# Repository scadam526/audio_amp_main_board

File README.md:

# audio_amp_main_board
Main board for a stereo 60W-per-channel amp. Includes four RCA analog L/R inputs, pre-amp input switching and volume control, main gain stage and output protection and muting.

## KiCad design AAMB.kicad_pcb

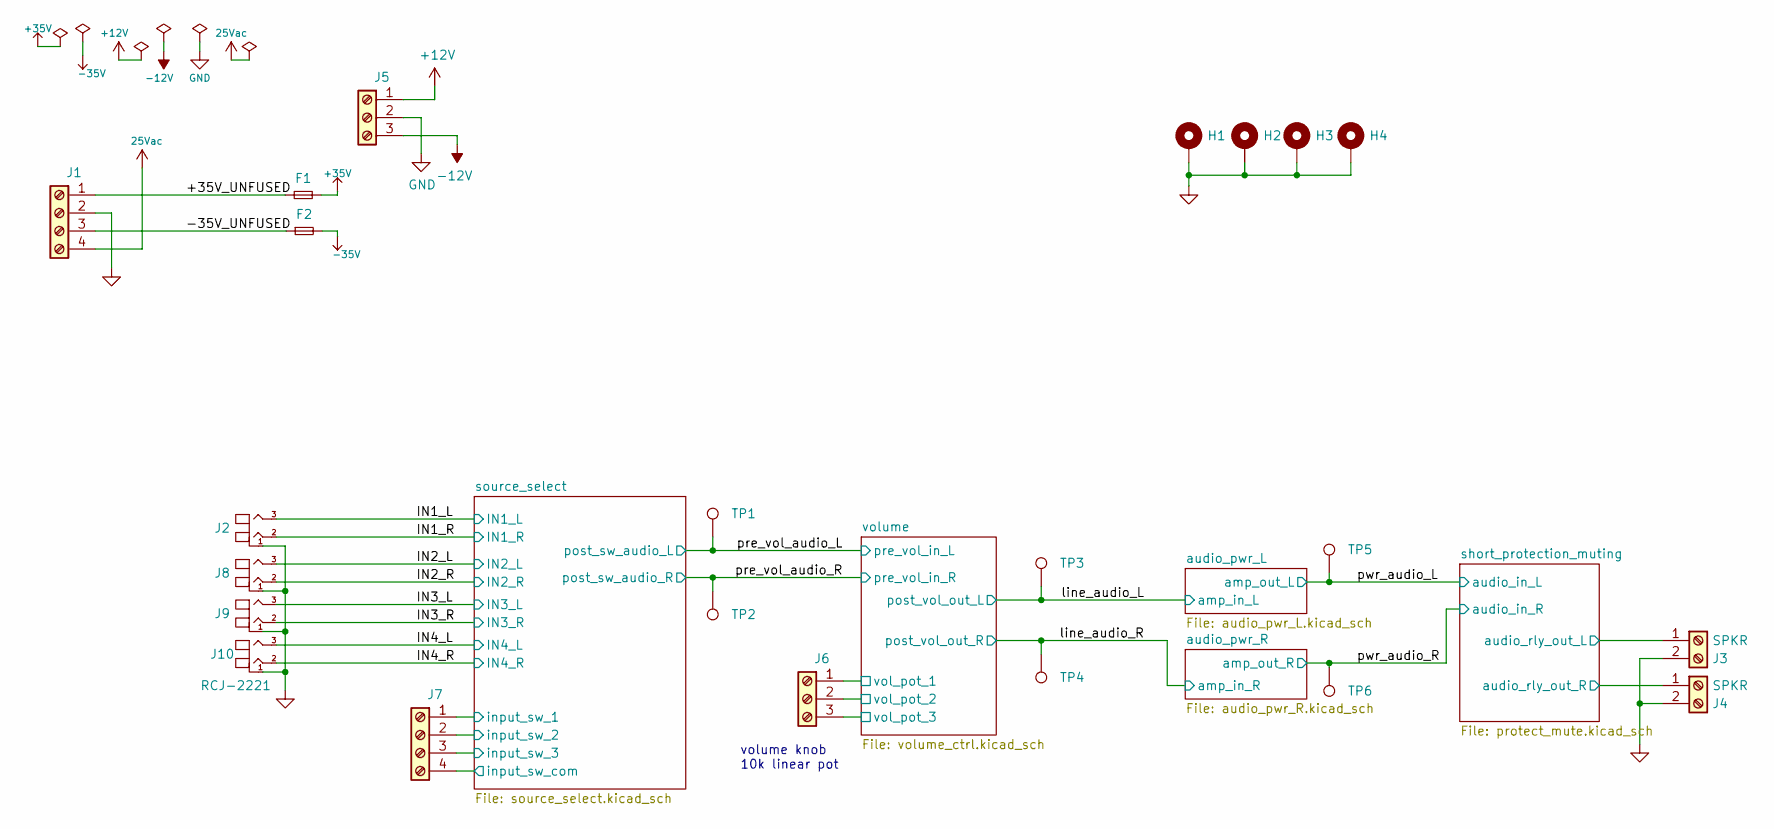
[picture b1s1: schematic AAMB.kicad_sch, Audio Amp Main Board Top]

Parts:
F1, F2: Fuse_Small; R_1206_3216Metric_Pad1.30x1.75mm_HandSolder; MPN C1F 3
H1, H2, H3, H4: MountingHole_Pad; MountingHole_3.2mm_M3_Pad
J1, J7: Screw_Terminal_01x04; TerminalBlock_Phoenix_MKDS-1,5-4_1x04_P5.00mm_Horizontal; MPN TB001-500-04BE
J2, J8, J9, J10: RCJ-2221
J3, J4: SPKR; TerminalBlock_Phoenix_MKDS-1,5-2_1x02_P5.00mm_Horizontal; MPN 1935161
J5, J6: Screw_Terminal_01x03; TerminalBlock_Phoenix_MKDS-1,5-3_1x03_P5.00mm_Horizontal; MPN 1935174
TP1, TP2, TP3, TP4, TP5, TP6: TestPoint; TestPoint_Keystone_5000-5004_Miniature

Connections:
25Vac: J1.4; also elsewhere on the board
+12V: J5.1; also elsewhere on the board
+35V: F1.2; also elsewhere on the board
-12V: J5.3; also elsewhere on the board
-35V: F2.2; also elsewhere on the board
/+35V_UNFUSED: F1.1, J1.1
/-35V_UNFUSED: F2.1, J1.3
/IN1_L: J2.3; also elsewhere on the board
/IN1_R: J2.2; also elsewhere on the board
/IN2_L: J8.3; also elsewhere on the board
/IN2_R: J8.2; also elsewhere on the board
/IN3_L: J9.3; also elsewhere on the board
/IN3_R: J9.2; also elsewhere on the board
/IN4_L: J10.3; also elsewhere on the board
/IN4_R: J10.2; also elsewhere on the board
/line_audio_L: TP3.1; also elsewhere on the board
/line_audio_R: TP4.1; also elsewhere on the board
/pre_vol_audio_L: TP1.1; also elsewhere on the board
/pre_vol_audio_R: TP2.1; also elsewhere on the board
/pwr_audio_L: TP5.1; also elsewhere on the board
/pwr_audio_R: TP6.1; also elsewhere on the board
/short_protection_muting/audio_rly_out_L: J3.1; also elsewhere on the board
/short_protection_muting/audio_rly_out_R: J4.1; also elsewhere on the board
/source_select/input_sw_1: J7.1; also elsewhere on the board
/source_select/input_sw_2: J7.2; also elsewhere on the board
/source_select/input_sw_3: J7.3; also elsewhere on the board
/source_select/input_sw_com: J7.4; also elsewhere on the board
/volume/vol_pot_1: J6.1; also elsewhere on the board
/volume/vol_pot_2: J6.2; also elsewhere on the board
/volume/vol_pot_3: J6.3; also elsewhere on the board
GND: H1.1, H2.1, H3.1, H4.1, J1.2, J2.1, J3.2, J4.2, J5.2, J8.1, J9.1, J10.1; also elsewhere on the board

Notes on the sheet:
volume knob 10k linear pot

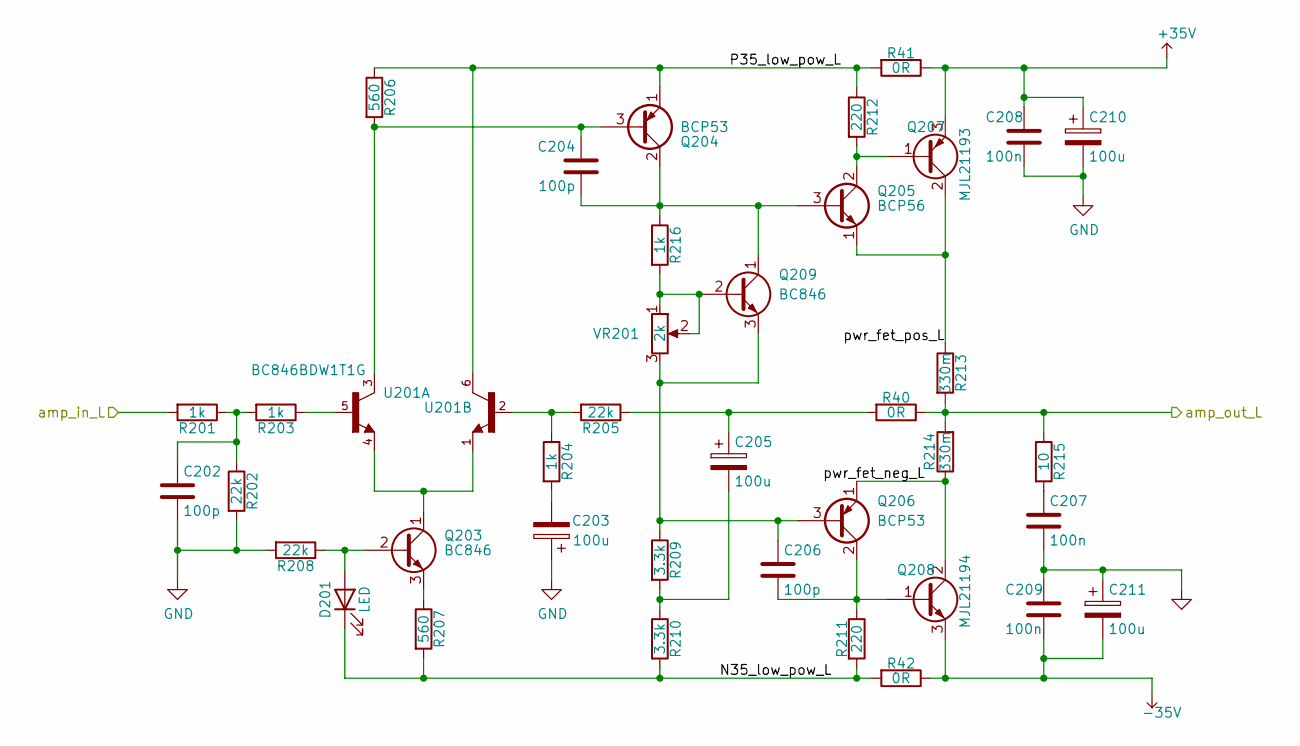
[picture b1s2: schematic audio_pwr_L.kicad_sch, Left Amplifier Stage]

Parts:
C202, C204, C206: 100p; C_0603_1608Metric_Pad1.08x0.95mm_HandSolder; MPN 885012006057
C203: 100u; C_Elec_5x5.4; MPN 865080142007
C205: 100u; C_Elec_6.3x7.7; MPN 865080545012
C207, C208, C209: 100n; C_Rect_L7.2mm_W4.5mm_P5.00mm_FKS2_FKP2_MKS2_MKP2; MPN R82EC3100AA70K
C210, C211: 100u; CP_Elec_10x10.5; MPN UUX1J101MNL1GS
D201: LED; LED_0603_1608Metric_Pad1.05x0.95mm_HandSolder; MPN SML-D12U1WT86
Q203, Q209: BC846; TO-92_Molded_Narrow; MPN BC846BLT1G
Q204, Q206: BCP53; TO-126_Vertical; MPN SBCP53-10T1G
Q205: BCP56; TO-126_Vertical; MPN SBCP56-16T3G
Q207: MJL21193; TO-264-3_Vertical; MPN MJL21193G
Q208: MJL21194; TO-264-3_Vertical; MPN MJL21194G
R40, R41, R42: 0R; R_2010_5025Metric; MPN RMCF1210ZT0R00
R201, R203, R204, R216: 1k; R_0201_0603Metric_Pad0.64x0.40mm_HandSolder; MPN RCS06031K00FKEA
R202, R205, R208: 22k; R_0201_0603Metric_Pad0.64x0.40mm_HandSolder; MPN CRGCQ0603F22K
R206, R207: 560; R_0201_0603Metric_Pad0.64x0.40mm_HandSolder; MPN CRGCQ0603F560R
R209, R210: 3.3k; R_0201_0603Metric_Pad0.64x0.40mm_HandSolder; MPN CRCW06033K30FKEA
R211, R212: 220; R_0201_0603Metric_Pad0.64x0.40mm_HandSolder; MPN ERJ-PA3F2200V
R213, R214: 330m; R_Radial_Power_L13.0mm_W9.0mm_P5.00mm; MPN SQMW5R33J
R215: 10; R_0201_0603Metric_Pad0.64x0.40mm_HandSolder; MPN ERJ-PA3F10R0V
U201: BC846BDW1T1G; SOT65P210X110-6N; MPN BC846BDW1T1G
VR201: 2k; Potentiometer_Bourns_3296W_Vertical; MPN 3296W-1-202LF

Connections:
+35V: C208.1, C210.1, Q207.3 (E), R41.1; also elsewhere on the board
-35V: C209.2, C211.2, Q208.3 (E), R42.1; also elsewhere on the board
/audio_pwr_L/N35_low_pow_L: D201.1 (K), R42.2, R207.2, R210.2, R211.2
/audio_pwr_L/P35_low_pow_L: Q204.1 (E), R41.2, R206.1, R212.1, U201.6 (COLLECTOR_2)
/audio_pwr_L/pwr_fet_neg_L: Q206.1 (E), Q208.2 (C), R214.1
/audio_pwr_L/pwr_fet_pos_L: Q205.1 (E), Q207.2 (C), R213.1
/line_audio_L: R201.2; also elsewhere on the board
/pwr_audio_L: R40.1, R213.2, R214.2, R215.1; also elsewhere on the board
GND: C202.2, C203.1, C207.2, C208.2, C209.1, C210.2, C211.1, R202.2, R208.2; also elsewhere on the board
unnamed: C202.1, R201.1, R202.1, R203.2
unnamed: C203.2, R204.2
unnamed: C204.1, Q204.3 (B), R206.2, U201.3 (COLLECTOR_1)
unnamed: C204.2, Q204.2 (C), Q205.3 (B), Q209.1 (C), R216.1
unnamed: C205.1, R40.2, R205.1
unnamed: C205.2, R209.2, R210.1
unnamed: C206.1, Q206.3 (B), Q209.3 (E), R209.1, VR201.3
unnamed: C206.2, Q206.2 (C), Q208.1 (B), R211.1
unnamed: C207.1, R215.2
unnamed: D201.2 (A), Q203.2 (B), R208.1
unnamed: Q203.1 (C), U201.1 (EMITTER_2), U201.4 (EMITTER_1)
unnamed: Q203.3 (E), R207.1
unnamed: Q205.2 (C), Q207.1 (B), R212.2
unnamed: Q209.2 (B), R216.2, VR201.1, VR201.2
unnamed: R203.1, U201.5 (BASE_1)
unnamed: R204.1, R205.2, U201.2 (BASE_2)

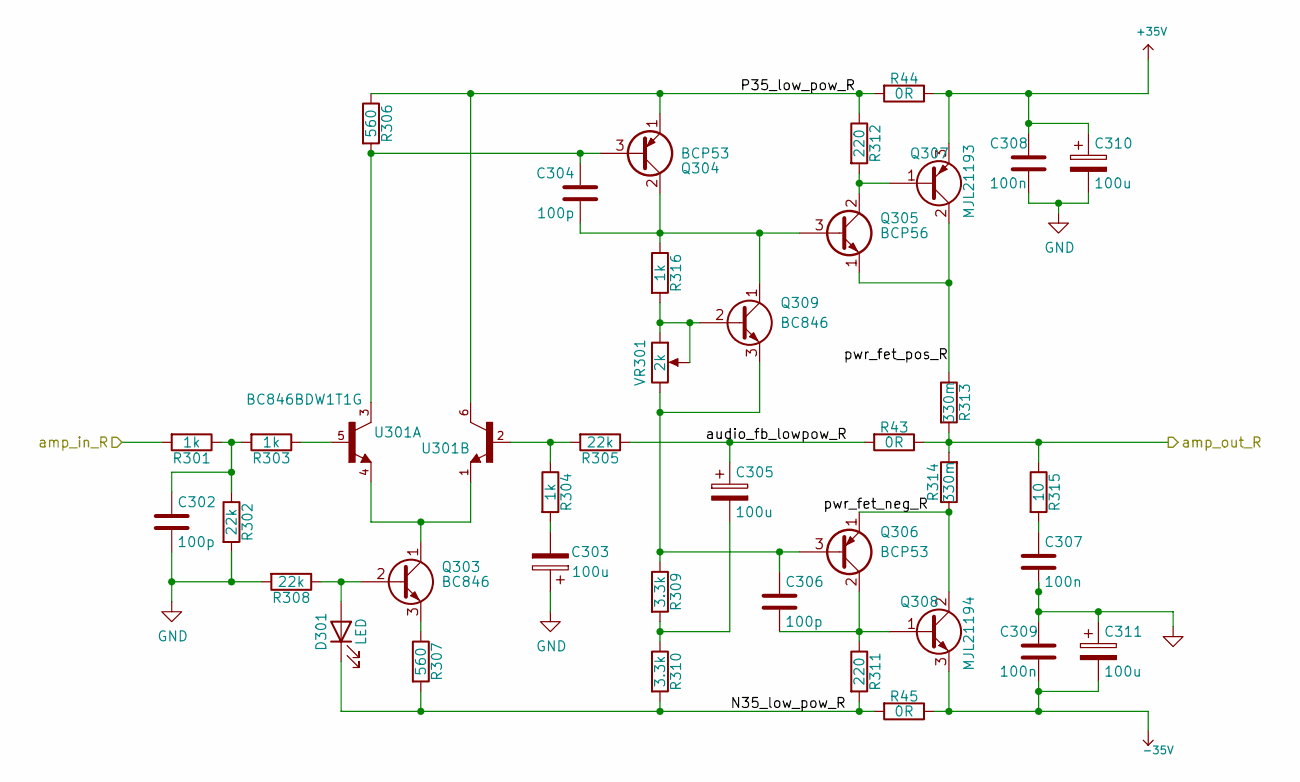
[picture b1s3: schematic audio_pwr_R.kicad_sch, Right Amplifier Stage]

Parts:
C302, C304, C306: 100p; C_0603_1608Metric_Pad1.08x0.95mm_HandSolder; MPN 885012006057
C303: 100u; C_Elec_5x5.4; MPN 865080142007
C305: 100u; C_Elec_6.3x7.7; MPN 865080545012
C307, C308, C309: 100n; C_Rect_L7.2mm_W4.5mm_P5.00mm_FKS2_FKP2_MKS2_MKP2; MPN R82EC3100AA70K
C310, C311: 100u; CP_Elec_10x10.5; MPN UUX1J101MNL1GS
D301: LED; LED_0603_1608Metric_Pad1.05x0.95mm_HandSolder; MPN SML-D12U1WT86
Q303, Q309: BC846; TO-92_Molded_Narrow; MPN BC846BLT1G
Q304, Q306: BCP53; TO-126_Vertical; MPN SBCP53-10T1G
Q305: BCP56; TO-126_Vertical; MPN SBCP56-16T3G
Q307: MJL21193; TO-264-3_Vertical; MPN MJL21193G
Q308: MJL21194; TO-264-3_Vertical; MPN MJL21194G
R43, R44, R45: 0R; R_2010_5025Metric; MPN RMCF1210ZT0R00
R301, R303, R304, R316: 1k; R_0201_0603Metric_Pad0.64x0.40mm_HandSolder; MPN RCS06031K00FKEA
R302, R305, R308: 22k; R_0201_0603Metric_Pad0.64x0.40mm_HandSolder; MPN CRGCQ0603F22K
R306, R307: 560; R_0201_0603Metric_Pad0.64x0.40mm_HandSolder; MPN CRGCQ0603F560R
R309, R310: 3.3k; R_0201_0603Metric_Pad0.64x0.40mm_HandSolder; MPN CRCW06033K30FKEA
R311, R312: 220; R_0201_0603Metric_Pad0.64x0.40mm_HandSolder; MPN ERJ-PA3F2200V
R313, R314: 330m; R_Radial_Power_L13.0mm_W9.0mm_P5.00mm; MPN SQMW5R33J
R315: 10; R_0201_0603Metric_Pad0.64x0.40mm_HandSolder; MPN ERJ-PA3F10R0V
U301: BC846BDW1T1G; SOT65P210X110-6N; MPN BC846BDW1T1G
VR301: 2k; Potentiometer_Bourns_3296W_Vertical; MPN 3296W-1-202LF

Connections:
+35V: C308.1, C310.1, Q307.3 (E), R44.1; also elsewhere on the board
-35V: C309.2, C311.2, Q308.3 (E), R45.1; also elsewhere on the board
/audio_pwr_R/N35_low_pow_R: D301.1 (K), R45.2, R307.2, R310.2, R311.2
/audio_pwr_R/P35_low_pow_R: Q304.1 (E), R44.2, R306.1, R312.1, U301.6 (COLLECTOR_2)
/audio_pwr_R/pwr_fet_neg_R: Q306.1 (E), Q308.2 (C), R314.1
/audio_pwr_R/pwr_fet_pos_R: Q305.1 (E), Q307.2 (C), R313.1
/line_audio_R: R301.2; also elsewhere on the board
/pwr_audio_R: R43.1, R313.2, R314.2, R315.1; also elsewhere on the board
GND: C302.2, C303.1, C307.2, C308.2, C309.1, C310.2, C311.1, R302.2, R308.2; also elsewhere on the board
unnamed: C302.1, R301.1, R302.1, R303.2
unnamed: C303.2, R304.2
unnamed: C304.1, Q304.3 (B), R306.2, U301.3 (COLLECTOR_1)
unnamed: C304.2, Q304.2 (C), Q305.3 (B), Q309.1 (C), R316.1
unnamed: C305.1, R43.2, R305.1
unnamed: C305.2, R309.2, R310.1
unnamed: C306.1, Q306.3 (B), Q309.3 (E), R309.1, VR301.3
unnamed: C306.2, Q306.2 (C), Q308.1 (B), R311.1
unnamed: C307.1, R315.2
unnamed: D301.2 (A), Q303.2 (B), R308.1
unnamed: Q303.1 (C), U301.1 (EMITTER_2), U301.4 (EMITTER_1)
unnamed: Q303.3 (E), R307.1
unnamed: Q305.2 (C), Q307.1 (B), R312.2
unnamed: Q309.2 (B), R316.2, VR301.1, VR301.2
unnamed: R303.1, U301.5 (BASE_1)
unnamed: R304.1, R305.2, U301.2 (BASE_2)

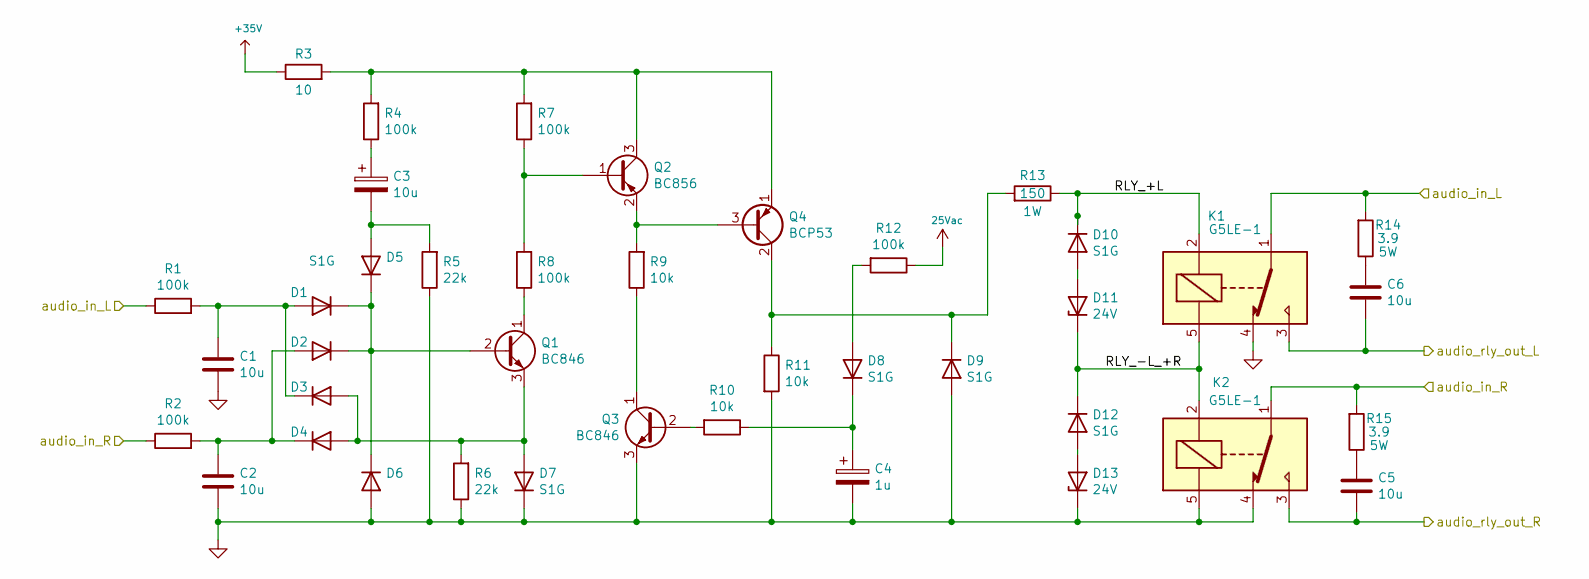
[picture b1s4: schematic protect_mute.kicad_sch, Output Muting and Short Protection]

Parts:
C1, C2, C5, C6: 10u; C_1206_3216Metric; MPN GRT31CR61H106KE01L
C3: 10u; CP_Elec_5x3; MPN 865080642006
C4: 1u; CP_Elec_4x5.4; MPN 865060640001
D1, D2, D3, D4, D5, D6, D7, D8, D9, D10, D12: S1G; D_DO-41_SOD81_P10.16mm_Horizontal; MPN S1G
D11, D13: 24V; D_SMA; MPN 1SMA5934BT3G
K1, K2: G5LE-1; Relay_SPDT_Omron-G5LE-1; MPN G5LE-1-VDDC12
Q1, Q3: BC846; TO-92_Inline; MPN BC846BLT1G
Q2: BC856; SOT-23; MPN BC856BLT3G
Q4: BCP53; TO-126-3_Vertical; MPN SBCP53-10T1G
R1, R2, R4, R7, R8, R12: 100k; R_0201_0603Metric_Pad0.64x0.40mm_HandSolder; MPN MCT06030C1003FP500
R3: 10; R_0201_0603Metric_Pad0.64x0.40mm_HandSolder; MPN ERJ-PA3F10R0V
R5, R6: 22k; R_0201_0603Metric_Pad0.64x0.40mm_HandSolder; MPN CRGCQ0603F22K
R9, R10, R11: 10k; R_0201_0603Metric_Pad0.64x0.40mm_HandSolder; MPN CRGCQ0603F10K
R13: 150; R_2512_6332Metric; MPN CRCW2512150RFKEG
R14, R15: 3.9; R_Axial_DIN0918_L18.0mm_D9.0mm_P7.62mm_Vertical; MPN SQPW53R9J

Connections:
25Vac: R12.1; also elsewhere on the board
+35V: R3.1; also elsewhere on the board
/pwr_audio_L: K1.1, R1.1, R14.2; also elsewhere on the board
/pwr_audio_R: K2.1, R2.1, R15.2; also elsewhere on the board
/short_protection_muting/RLY_+L: D10.1 (K), K1.2, R13.1
/short_protection_muting/RLY_-L_+R: D11.1 (K), D12.1 (K), K1.5, K2.2
/short_protection_muting/audio_rly_out_L: C6.2, K1.3; also elsewhere on the board
/short_protection_muting/audio_rly_out_R: C5.2, K2.3; also elsewhere on the board
GND: C1.2, C2.2, C4.2, D6.2 (A), D7.1 (K), D9.2 (A), D13.1 (K), K1.4, K2.4, K2.5, Q3.3 (E), R5.1, R6.1, R11.2; also elsewhere on the board
unnamed: C1.1, D1.2 (A), D3.1 (K), R1.2
unnamed: C2.1, D2.2 (A), D4.1 (K), R2.2
unnamed: C3.1, R4.1
unnamed: C3.2, D5.2 (A), R5.2
unnamed: C4.1, D8.1 (K), R10.1
unnamed: C5.1, R15.1
unnamed: C6.1, R14.1
unnamed: D1.1 (K), D2.1 (K), D5.1 (K), D6.1 (K), Q1.2 (B)
unnamed: D3.2 (A), D4.2 (A), D7.2 (A), Q1.3 (E), R6.2
unnamed: D8.2 (A), R12.2
unnamed: D9.1 (K), Q4.2 (C), R11.1, R13.2
unnamed: D10.2 (A), D11.2 (A)
unnamed: D12.2 (A), D13.2 (A)
unnamed: Q1.1 (C), R8.1
unnamed: Q2.1 (B), R7.1, R8.2
unnamed: Q2.2 (E), Q4.3 (B), R9.2
unnamed: Q2.3 (C), Q4.1 (E), R3.2, R4.2, R7.2
unnamed: Q3.1 (C), R9.1
unnamed: Q3.2 (B), R10.2

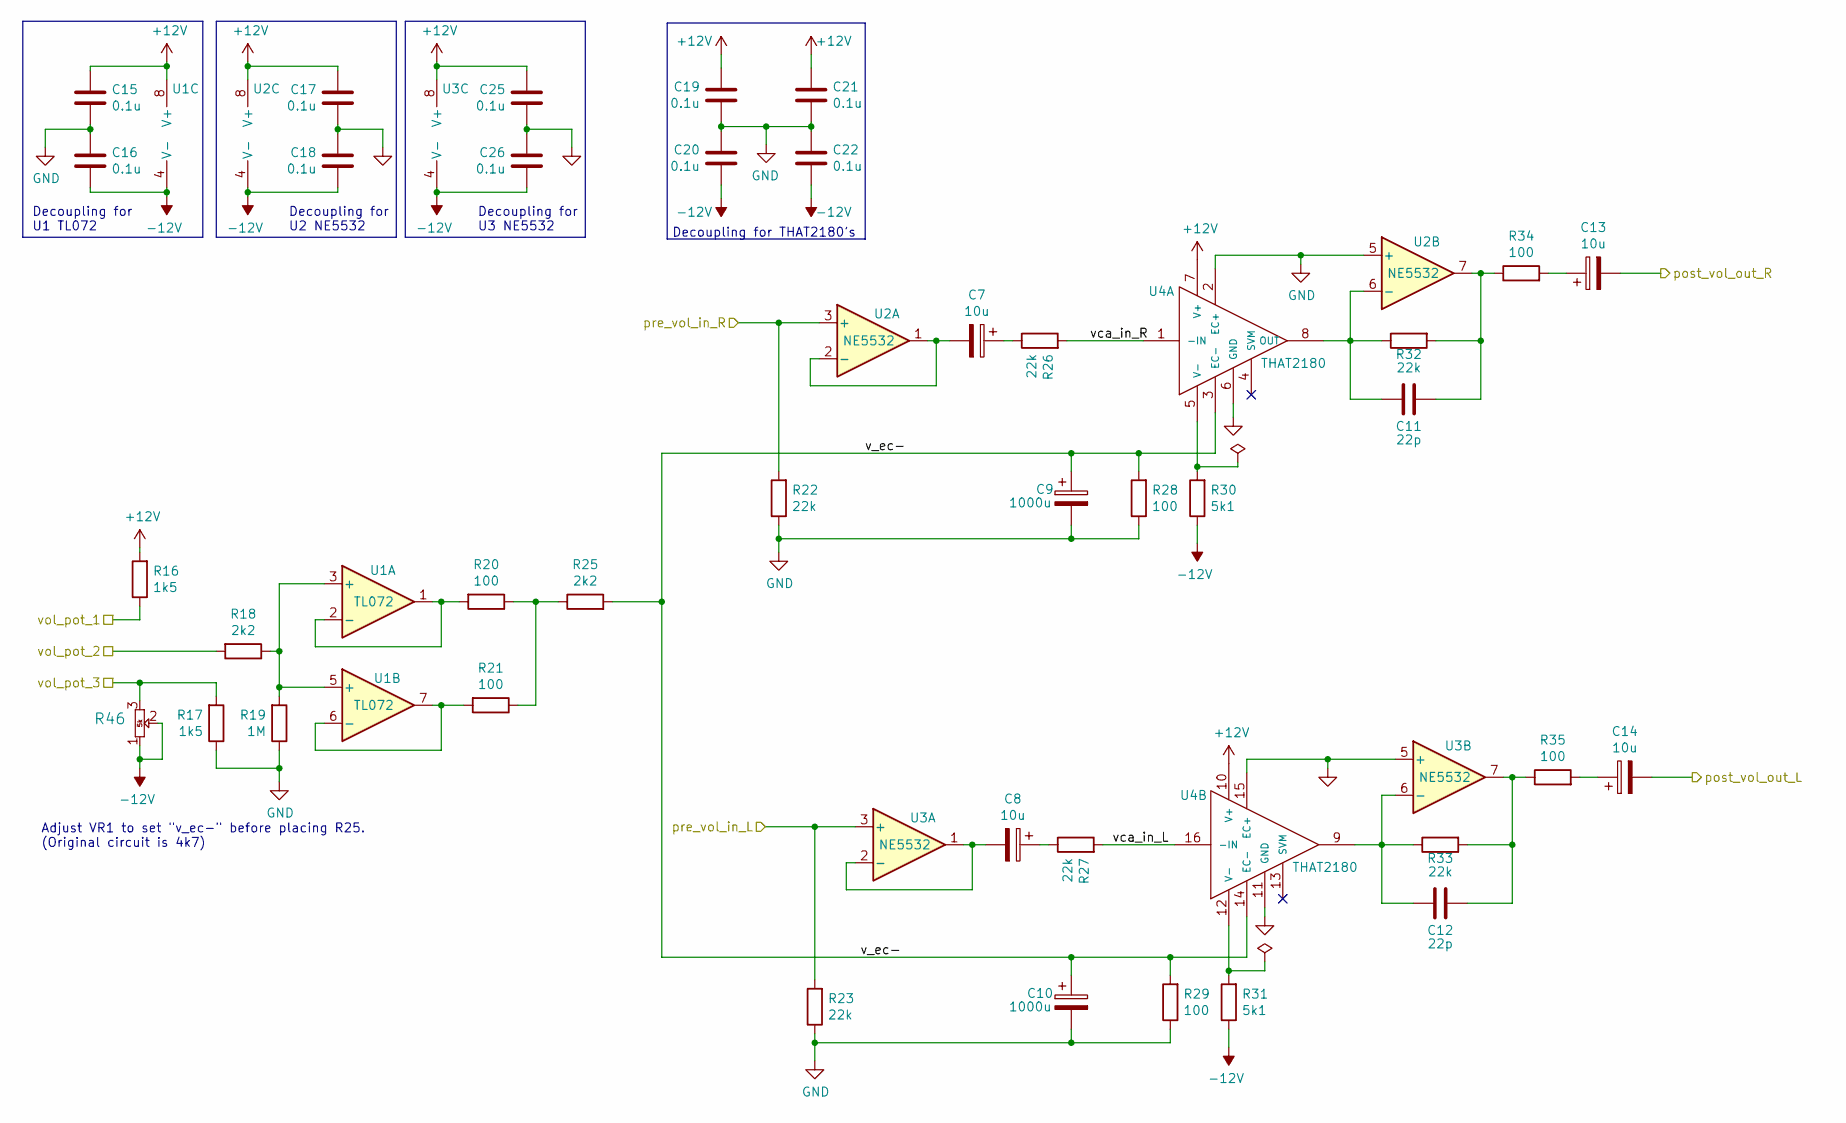
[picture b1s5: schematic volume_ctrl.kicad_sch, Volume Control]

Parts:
C7, C8, C13, C14: 10u; CP_Elec_5x3; MPN 865080642006
C9, C10: 1000u; C_Elec_10x10.2; MPN EEV-FK1E102Q
C11, C12: 22p; C_0603_1608Metric_Pad1.08x0.95mm_HandSolder; MPN 885012006053
C15, C16, C17, C18, C19, C20, C21, C22, C25, C26: 0.1u; C_0603_1608Metric_Pad1.08x0.95mm_HandSolder; MPN C0603C104Z3VACTU
R16, R17: 1k5; R_0201_0603Metric_Pad0.64x0.40mm_HandSolder; MPN ERJ-3EKF1501V
R18, R25: 2k2; R_0201_0603Metric_Pad0.64x0.40mm_HandSolder; MPN CRGCQ0603F2K2
R19: 1M; R_0201_0603Metric_Pad0.64x0.40mm_HandSolder; MPN ERJ-3EKF1004V
R20, R21, R28, R29, R34, R35: 100; R_0201_0603Metric_Pad0.64x0.40mm_HandSolder; MPN RCS0603100RFKEA
R22, R23, R26, R27, R32, R33: 22k; R_0201_0603Metric_Pad0.64x0.40mm_HandSolder; MPN CRGCQ0603F22K
R30, R31: 5k1; R_0201_0603Metric_Pad0.64x0.40mm_HandSolder; MPN ERJ-PA3F5101V
R46: 3203X502P; 3203X502P_TEC
U1: TL072; SOIC-8_3.9x4.9mm_P1.27mm; MPN TL072CDT
U2, U3: NE5532; SOIC-8_3.9x4.9mm_P1.27mm; MPN NE5532DR
U4: THAT2180; DIP-16_W7.62mm_SMDSocket_SmallPads; MPN 214-99-316-01-670800

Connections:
+12V: C15.1, C17.1, C19.1, C21.1, C25.1, R16.2, U1.8 (V+), U2.8 (V+), U3.8 (V+), U4.7 (V+), U4.10 (V+); also elsewhere on the board
-12V: C16.2, C18.2, C20.2, C22.2, C26.2, R30.1, R31.1, R46.1, R46.2, U1.4 (V-), U2.4 (V-), U3.4 (V-); also elsewhere on the board
/line_audio_L: C14.2; also elsewhere on the board
/line_audio_R: C13.2; also elsewhere on the board
/pre_vol_audio_L: R23.2, U3.3 (+); also elsewhere on the board
/pre_vol_audio_R: R22.2, U2.3 (+); also elsewhere on the board
/volume/v_ec-: C9.1, C10.1, R25.2, R28.2, R29.2, U4.3 (EC-), U4.14 (EC-)
/volume/vca_in_L: R27.2, U4.16 (-IN)
/volume/vca_in_R: R26.2, U4.1 (-IN)
/volume/vol_pot_1: R16.1; also elsewhere on the board
/volume/vol_pot_2: R18.2; also elsewhere on the board
/volume/vol_pot_3: R17.2, R46.3; also elsewhere on the board
GND: C9.2, C10.2, C15.2, C16.1, C17.2, C18.1, C19.2, C20.1, C21.2, C22.1, C25.2, C26.1, R17.1, R19.1, R22.1, R23.1, R28.1, R29.1, U2.5 (+), U3.5 (+), U4.2 (EC+), U4.6 (GND), U4.11 (GND), U4.15 (EC+); also elsewhere on the board
unnamed: C7.1, R26.1
unnamed: C7.2, U2.1, U2.2 (-)
unnamed: C8.1, R27.1
unnamed: C8.2, U3.1, U3.2 (-)
unnamed: C11.1, R32.2, R34.1, U2.7
unnamed: C11.2, R32.1, U2.6 (-), U4.8 (OUT)
unnamed: C12.1, R33.2, R35.1, U3.7
unnamed: C12.2, R33.1, U3.6 (-), U4.9
unnamed: C13.1, R34.2
unnamed: C14.1, R35.2
unnamed: R18.1, R19.2, U1.3 (+), U1.5 (+)
unnamed: R20.1, R21.1, R25.1
unnamed: R20.2, U1.1, U1.2 (-)
unnamed: R21.2, U1.6 (-), U1.7
unnamed: R30.2, U4.5 (V-)
unnamed: R31.2, U4.12 (V-)

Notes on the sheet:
Adjust VR1 to set "v_ec-" before placing R25. (Original circuit is 4k7)
Decoupling for U1 TL072
Decoupling for U2 NE5532
Decoupling for U3 NE5532
Decoupling for THAT2180's

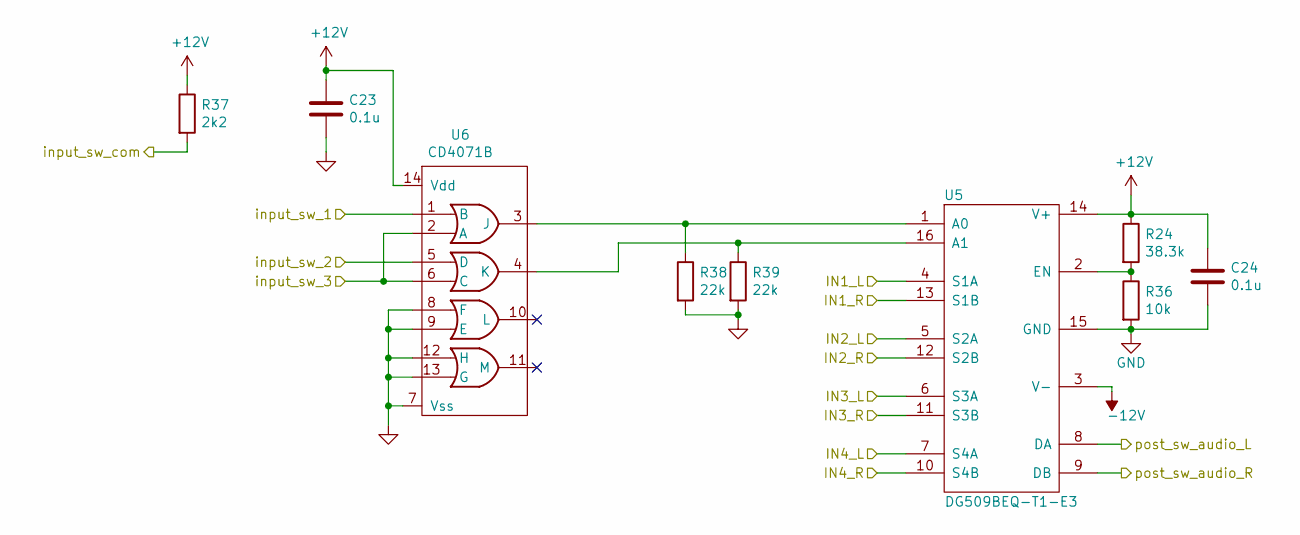
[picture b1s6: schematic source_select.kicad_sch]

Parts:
C23, C24: 0.1u; C_0603_1608Metric_Pad1.08x0.95mm_HandSolder; MPN C0603C104Z3VACTU
R24: 38.3k; R_0201_0603Metric_Pad0.64x0.40mm_HandSolder; MPN ERJ-3EKF3832V
R36: 10k; R_0201_0603Metric_Pad0.64x0.40mm_HandSolder; MPN CRGCQ0603F10K
R37: 2k2; R_0201_0603Metric_Pad0.64x0.40mm_HandSolder; MPN CRGCQ0603F2K2
R38, R39: 22k; R_0201_0603Metric_Pad0.64x0.40mm_HandSolder; MPN CRGCQ0603F22K
U5: DG509BEQ-T1-E3; TSSOP-16_4.4x5mm_P0.65mm; MPN DG509BEQ-T1-E3
U6: CD4071B; SOIC-14_3.9x8.7mm_P1.27mm; MPN CD4071BM96

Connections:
+12V: C23.1, C24.1, R24.1, R37.1, U5.14 (V+), U6.14 (Vdd); also elsewhere on the board
-12V: U5.3 (V-); also elsewhere on the board
/IN1_L: U5.4 (S1A); also elsewhere on the board
/IN1_R: U5.13 (S1B); also elsewhere on the board
/IN2_L: U5.5 (S2A); also elsewhere on the board
/IN2_R: U5.12 (S2B); also elsewhere on the board
/IN3_L: U5.6 (S3A); also elsewhere on the board
/IN3_R: U5.11 (S3B); also elsewhere on the board
/IN4_L: U5.7 (S4A); also elsewhere on the board
/IN4_R: U5.10 (S4B); also elsewhere on the board
/pre_vol_audio_L: U5.8 (DA); also elsewhere on the board
/pre_vol_audio_R: U5.9 (DB); also elsewhere on the board
/source_select/input_sw_1: U6.1 (B); also elsewhere on the board
/source_select/input_sw_2: U6.5 (D); also elsewhere on the board
/source_select/input_sw_3: U6.2 (A), U6.6 (C); also elsewhere on the board
/source_select/input_sw_com: R37.2; also elsewhere on the board
GND: C23.2, C24.2, R36.2, R38.2, R39.2, U5.15 (GND), U6.7 (Vss), U6.8 (F), U6.9 (E), U6.12 (H), U6.13 (G); also elsewhere on the board
unnamed: R24.2, R36.1, U5.2 (EN)
unnamed: R38.1, U5.1 (A0), U6.3 (J)
unnamed: R39.1, U5.16 (A1), U6.4 (K)

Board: 6 copper layers, 191 parts (26 on the bottom side), 114 nets, no tracks yet.

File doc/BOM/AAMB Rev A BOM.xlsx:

Ref | Qnty | MFG | MPN | Value | Footprint
C1, C5, C6, C2, | 4 | Murata Electronics | GRT31CR61H106KE01L | 10u | Capacitor_SMD:C_1206_3216Metric
C4, | 1 | Wurth Elektronik | 865060640001 | 1u | Capacitor_SMD:CP_Elec_4x5.4
C8, C14, C7, C13, C3, | 5 | Wurth Elektronik | 865080642006 | 10u | Capacitor_SMD:CP_Elec_5x3
C9, C10, | 2 | Panasonic Electronic Components | EEV-FK1E102Q | 1000u | Capacitor_SMD:C_Elec_10x10.2
C12, C11, | 2 | Wurth Elektronik | 885012006053 | 22p | Capacitor_SMD:C_0603_1608Metric_Pad1.05x0.95mm_HandSolder
C15, C16, C17, C18, C19, C20, C21, C22, C25, C26, C23, C24, | 12 | KEMET | C0603C104Z3VACTU | 0.1u | Capacitor_SMD:C_0603_1608Metric_Pad1.05x0.95mm_HandSolder
C202, C206, C204, C302, C306, C304, | 6 | Wurth Elektronik | 885012006057 | 100p | Capacitor_SMD:C_0603_1608Metric_Pad1.05x0.95mm_HandSolder
C203, C303, | 2 | Wurth Elektronik | 865080142007 | 100u | Capacitor_SMD:C_Elec_5x5.4
C205, C305, | 2 | Wurth Elektronik | 865080545012 | 100u | Capacitor_SMD:C_Elec_6.3x7.7
C207, C209, C208, C307, C309, C308, | 6 | KEMET | R82EC3100AA70K | 100n | Capacitor_THT:C_Rect_L7.2mm_W4.5mm_P5.00mm_FKS2_FKP2_MKS2_MKP2
C211, C210, C311, C310, | 4 | Nichicon | UUX1J101MNL1GS | 100u | Capacitor_SMD:CP_Elec_10x10.5
D12, D10, D5, D9, D8, D7, D6, D4, D3, D2, D1, | 11 | ON Semiconductor | S1G | S1G | Diode_SMD:D_SMA
D13, D11, | 2 | ON Semiconductor | 1SMA5934BT3G | 24V | Diode_SMD:D_SMA
D201, D301, | 2 | Rohm Semiconductor | SML-D12U1WT86 | LED | LED_SMD:LED_0603_1608Metric_Pad1.05x0.95mm_HandSolder
F2, F1, | 2 | Bel Fuse Inc. | C1F 3 | Fuse_Small | Resistor_SMD:R_1206_3216Metric_Pad1.42x1.75mm_HandSolder
J1, J7, | 2 | CUI Devices | TB001-500-04BE | Screw_Terminal_01x04 | TerminalBlock_Phoenix:TerminalBlock_Phoenix_MKDS-1,5-4_1x04_P5.00mm_Horizontal
J2, | 1 | Switchcraft Inc. | PJRAS4X2U01X | PJRAS4X2U01X | Connectors-amp:PJRAS4X2U01X
J4, J3, | 2 | Phoenix Contact | 1935161 | SPKR | TerminalBlock_Phoenix:TerminalBlock_Phoenix_MKDS-1,5-2_1x02_P5.00mm_Horizontal
J5, J6, | 2 | Phoenix Contact | 1935174 | Screw_Terminal_01x03 | TerminalBlock_Phoenix:TerminalBlock_Phoenix_MKDS-1,5-3_1x03_P5.00mm_Horizontal
K2, K1, | 2 | Omron Electronics Inc-EMC Div | G5LE-1-VDDC12 | G5LE-1 | Relay_THT:Relay_SPDT_Omron-G5LE-1
Q2, | 1 | ON Semiconductor | BC856BLT3G | BC856 | Package_TO_SOT_SMD:SOT-23
Q203, Q209, Q303, Q309, Q3, Q1, | 6 | ON Semiconductor | BC846BLT1G | BC846 | Package_TO_SOT_SMD:SOT-23
Q205, Q305, | 2 | ON Semiconductor | SBCP56-16T3G | BCP56 | Package_TO_SOT_SMD:SOT-223
Q206, Q204, Q306, Q304, Q4, | 5 | ON Semiconductor | SBCP53-10T1G | BCP53 | Package_TO_SOT_SMD:SOT-223
Q207, Q307, | 2 | ON Semiconductor | MJL21193G | MJL21193 | Package_TO_SOT_THT:TO-264-3_Vertical
Q208, Q308, | 2 | ON Semiconductor | MJL21194G | MJL21194 | Package_TO_SOT_THT:TO-264-3_Vertical
R2, R1, R7, R4, R8, R12, | 6 | Vishay Beyschlag | MCT06030C1003FP500 | 100k | Resistor_SMD:R_0603_1608Metric_Pad1.05x0.95mm_HandSolder
R13, | 1 | Vishay Dale | CRCW2512150RFKEG | 150 | Resistor_SMD:R_2512_6332Metric
R14, R15, | 2 | TE Connectivity Passive Product | SQPW53R9J | 3.9 | Resistor_THT:R_Axial_DIN0918_L18.0mm_D9.0mm_P7.62mm_Vertical
R16, R17, | 2 | Panasonic Electronic Components | ERJ-3EKF1501V | 1k5 | Resistor_SMD:R_0603_1608Metric_Pad1.05x0.95mm_HandSolder
R19, | 1 | Panasonic Electronic Components | ERJ-3EKF1004V | 1M | Resistor_SMD:R_0603_1608Metric_Pad1.05x0.95mm_HandSolder
R24, | 1 | Panasonic Electronic Components | ERJ-3EKF3832V | 38.3k | Resistor_SMD:R_0603_1608Metric_Pad1.05x0.95mm_HandSolder
R25, R18, R37, | 3 | TE Connectivity Passive Product | CRGCQ0603F2K2 | 2k2 | Resistor_SMD:R_0603_1608Metric_Pad1.05x0.95mm_HandSolder
R31, R30, | 2 | Panasonic Electronic Components | ERJ-PA3F5101V | 5k1 | Resistor_SMD:R_0603_1608Metric_Pad1.05x0.95mm_HandSolder
R35, R20, R21, R29, R34, R28, | 6 | Vishay Dale | RCS0603100RFKEA | 100 | Resistor_SMD:R_0603_1608Metric_Pad1.05x0.95mm_HandSolder
R36, R9, R10, R11, | 4 | TE Connectivity Passive Product | CRGCQ0603F10K | 10k | Resistor_SMD:R_0603_1608Metric_Pad1.05x0.95mm_HandSolder
R42, R41, R40, R45, R44, R43, | 6 | Stackpole Electronics Inc | RMCF1210ZT0R00 | 0R | Resistor_SMD:R_2010_5025Metric_Pad1.52x2.65mm_HandSolder
R201, R204, R216, R203, R303, R301, R304, R316, | 8 | Vishay Dale | RCS06031K00FKEA | 1k | Resistor_SMD:R_0603_1608Metric_Pad1.05x0.95mm_HandSolder
R202, R208, R205, R302, R308, R305, R27, R23, R33, R26, R22, R32, R38, R39, R6,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 | 16 | TE Connectivity Passive Product | CRGCQ0603F22K | 22k | Resistor_SMD:R_0603_1608Metric_Pad1.05x0.95mm_HandSolder
R207, R206, R307, R306, | 4 | TE Connectivity Passive Product | CRGCQ0603F560R | 560 | Resistor_SMD:R_0603_1608Metric_Pad1.05x0.95mm_HandSolder
R210, R209, R310, R309, | 4 | Vishay Dale | CRCW06033K30FKEA | 3.3k | Resistor_SMD:R_0603_1608Metric_Pad1.05x0.95mm_HandSolder
R211, R212, R311, R312, | 4 | Panasonic Electronic Components | ERJ-PA3F2200V | 220 | Resistor_SMD:R_0603_1608Metric_Pad1.05x0.95mm_HandSolder
R214, R213, R314, R313, | 4 | TE Connectivity Passive Product | SQMW5R33J | 330m | Resistor_THT:R_Radial_Power_L13.0mm_W9.0mm_P5.00mm
R215, R315, R3, | 3 | Panasonic Electronic Components | ERJ-PA3F10R0V | 10 | Resistor_SMD:R_0603_1608Metric_Pad1.05x0.95mm_HandSolder
TP1, TP2, TP3, TP4, TP5, TP6, | 6 |  |  | TP | TestPoint:TestPoint_2Pads_Pitch2.54mm_Drill0.8mm
U1, | 1 | STMicroelectronics | TL072CDT | TL072 | Package_SO:SOIC-8_3.9x4.9mm_P1.27mm
U3, U2, | 2 | Texas Instruments | NE5532DR | NE5532 | Package_SO:SOIC-8_3.9x4.9mm_P1.27mm
U4, | 1 | Mill-Max Manufacturing Corp. | 214-99-316-01-670800 | THAT2180 | Package_DIP:DIP-16_W7.62mm_SMDSocket_SmallPads
U5, | 1 | Vishay Siliconix | DG509BEQ-T1-E3 | DG509BEQ-T1-E3 | Package_SO:TSSOP-16_4.4x5mm_P0.65mm
U6, | 1 | Texas Instruments | CD4071BM96 | CD4071B | Package_SO:SOIC-14_3.9x8.7mm_P1.27mm
U201, U301, | 2 | ON Semiconductor | BC846BDW1T1G | BC846BDW1T1G | Package_TO_SOT_SMD:SOT-363_SC-70-6
VR1, | 1 | Nidec Copal Electronics | CT6EP202 | 5k | Potentiometer_THT:Nidec_CT6EP202
VR201, VR301, | 2 | Bourns Inc. | 3296W-1-202LF | 2k | Potentiometer_THT:Potentiometer_Bourns_3296W_Vertical

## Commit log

2020-01-20 Initial commit of working directory.
2020-01-20 Began placing volume circuit parts, placed a trim pot for R17 to allow pre-amp level adjustment.
2020-01-21 Volume circuit placed and connected. Page titles added.
2020-01-21 Deleted soft start circuit. Not needed right now.
2020-01-21 Deleted obsolete left and right channel schematics.
2020-01-21 Started input select circuit.
2020-01-22 Opened on home office computer. Some rescue and lib conversion happened. Need to confirm no changes on work laptop.
2020-01-22 Fixed several DRC errors. Tied audoi input returns to GND. Added Switch logic.
2020-01-22 Schecmatic cleanup.
2020-01-23 Added test points. Schematic cleanup.
2020-01-23 Cleaning up user configs.
2020-01-23 Testing branch. Pulled parts into layout.
2020-01-23 23JAN2020 daily commit.
2020-01-24 Some layout progress. Nightly commit.
2020-01-24 24JAN2020 daily
2020-01-25 Daily commit and ready to merge back to master.
2020-01-27 26JAN2020 nightly. Continued placement arangment.
2020-01-27 Prep to merge.
2020-01-27 Layout progress
2020-01-27 Just before autoroute. DRC's not addressed.
2020-01-28 First pass auto-route
2020-01-28 First pass layout. Needs DRC errors address for next pass.
2020-01-31 Daily. 4-layer layout done. Only one no-connect.
2020-01-31 Manual layout started.
2020-02-02 Linux test and some layout progress.
2020-02-04 Routing complete. Needs silscreen cleanup and screw holes placed.
2020-02-04 Added screw holes.
2020-02-06 Ready to clean up silkscreen. Need to open in windows and make library table references and not direct file pointers.
2020-02-06 Some silkscreen progress. Windows already setup to use library references. Use config paths in linux to set them up too.
2020-02-08 Generated fab files for quote test.
2020-04-06 Silkscreen cleanup. Rev A release candidate.
2020-04-09 Lots of part changes to SMD devices. Adding MPN, MFG to all parts for BOM export.
2020-04-10 Layout startover, sorting, some routing. Removed redundant fuses. BOM export.
2020-04-11 Layout progress. Added two missing decoupling caps.
2020-04-16 Capturing layout progress.
2020-04-21 Place and route complete. Silkscreen cleanup needed.
2020-04-22 Layout complete. Screw holes added and connected to GND.
2020-04-22 Adding BOM file.
2023-02-07 Updating files with Rev02
2023-02-11 Minor layout updates.
2023-03-01 Updating layout and various changes. Backup commit.

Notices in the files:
parts and their libraries:
Copyright 2021 Accelerated Designs. All rights reserved.
